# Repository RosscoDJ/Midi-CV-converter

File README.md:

# Midi-CV-converter
Arduino based Midi to CV converter, including selectable Midi channel.

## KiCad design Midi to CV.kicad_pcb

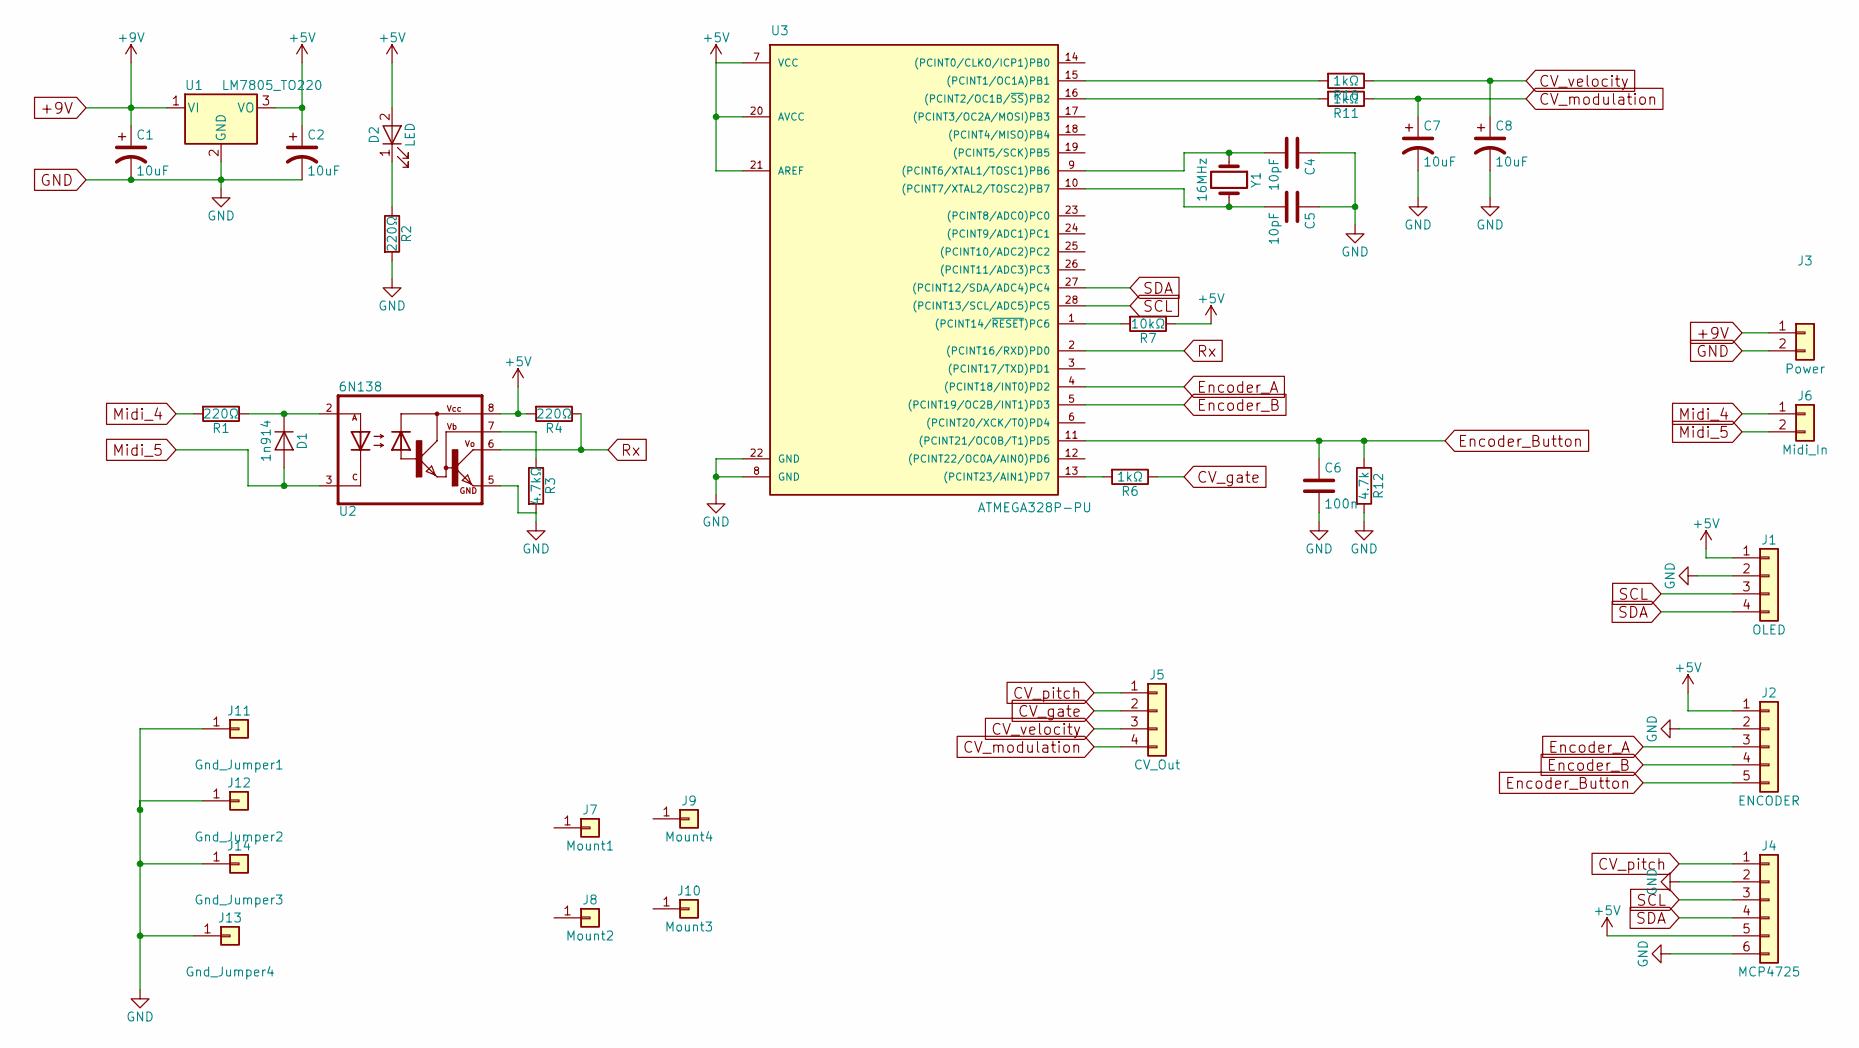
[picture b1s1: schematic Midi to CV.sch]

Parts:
C1, C2, C7, C8: 10uF; CP_Radial_D4.0mm_P1.50mm
C4, C5: 10pF; C_Disc_D6.0mm_W2.5mm_P5.00mm
C6: 100n; C_Disc_D6.0mm_W2.5mm_P5.00mm
D1: 1n914; D_DO-35_SOD27_P7.62mm_Horizontal
D2: LED; LED_D5.0mm
J1: OLED; Pin_Header_Straight_1x04_Pitch2.54mm
J2: ENCODER; Pin_Header_Straight_1x05_Pitch2.54mm
J3: Power; Pin_Header_Straight_1x02_Pitch2.54mm
J4: MCP4725; Pin_Header_Straight_1x06_Pitch2.54mm
J5: CV_Out; Pin_Header_Straight_1x04_Pitch2.54mm
J6: Midi_In; Pin_Header_Straight_1x02_Pitch2.54mm
J7: Mount1; MountingHole_3.2mm_M3
J8: Mount2; MountingHole_3.2mm_M3
J9: Mount4; MountingHole_3.2mm_M3
J10: Mount3; MountingHole_3.2mm_M3
J11: Gnd_Jumper1; Pin_Header_Straight_1x01_Pitch2.54mm
J12: Gnd_Jumper2; Pin_Header_Straight_1x01_Pitch2.54mm
J13: Gnd_Jumper4; Pin_Header_Straight_1x01_Pitch2.54mm
J14: Gnd_Jumper3; Pin_Header_Straight_1x01_Pitch2.54mm
R1, R2, R4: 220Ω; R_Axial_DIN0204_L3.6mm_D1.6mm_P7.62mm_Horizontal
R3: 4.7kΩ; R_Axial_DIN0204_L3.6mm_D1.6mm_P7.62mm_Horizontal
R6, R10, R11: 1kΩ; R_Axial_DIN0204_L3.6mm_D1.6mm_P7.62mm_Horizontal
R7: 10kΩ; R_Axial_DIN0204_L3.6mm_D1.6mm_P7.62mm_Horizontal
R12: 4.7k; R_Axial_DIN0204_L3.6mm_D1.6mm_P7.62mm_Horizontal
U1: LM7805_TO220; TO-220-3_Vertical
U2: 6N138; DIP-8_W7.62mm_LongPads
U3: ATMEGA328P-PU; DIP-28_W7.62mm_LongPads
Y1: 16MHz; Crystal_HC49-U_Vertical

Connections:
+5V: C2.1, D2.2 (A), J1.1, J2.1, J4.5, R4.2, R7.1, U1.3 (VO), U2.8 (VCC), U3.7 (VCC), U3.20 (AVCC), U3.21 (AREF)
+9V: C1.1, J3.1, U1.1 (VI)
CV_gate: J5.2, R6.1
CV_modulation: C7.1, J5.4, R11.1
CV_pitch: J4.1, J5.1
CV_velocity: C8.1, J5.3, R10.1
Encoder_A: J2.3, U3.4 ((PCINT18/INT0)PD2)
Encoder_B: J2.4, U3.5 ((PCINT19/OC2B/INT1)PD3)
Encoder_Button: C6.1, J2.5, R12.1, U3.11 ((PCINT21/OC0B/T1)PD5)
GND: C1.2, C2.2, C4.1, C5.1, C6.2, C7.2, C8.2, J1.2, J2.2, J3.2, J4.2, J4.6, J11.1, J12.1, J13.1, J14.1, R2.2, R3.2, R12.2, U1.2 (GND), U2.5 (GND), U3.8 (GND), U3.22 (GND)
Midi_4: J6.1, R1.2
Midi_5: D1.2 (A), J6.2, U2.3 (C)
unnamed: C4.2, U3.9 ((PCINT6/XTAL1/TOSC1)PB6), Y1.1
unnamed: C5.2, U3.10 ((PCINT7/XTAL2/TOSC2)PB7), Y1.2
unnamed: D1.1 (K), R1.1, U2.2 (A)
unnamed: D2.1 (K), R2.1
unnamed: R3.1, U2.7 (VB)
unnamed: R6.2, U3.13 ((PCINT23/AIN1)PD7)
unnamed: R7.2, U3.1 ((PCINT14/~RESET~)PC6)
unnamed: R10.2, U3.15 ((PCINT1/OC1A)PB1)
unnamed: R11.2, U3.16 ((PCINT2/OC1B/~SS~)PB2)
Rx: R4.1, U2.6 (VO), U3.2 ((PCINT16/RXD)PD0)
SCL: J1.3, J4.3, U3.28 ((PCINT13/SCL/ADC5)PC5)
SDA: J1.4, J4.4, U3.27 ((PCINT12/SDA/ADC4)PC4)

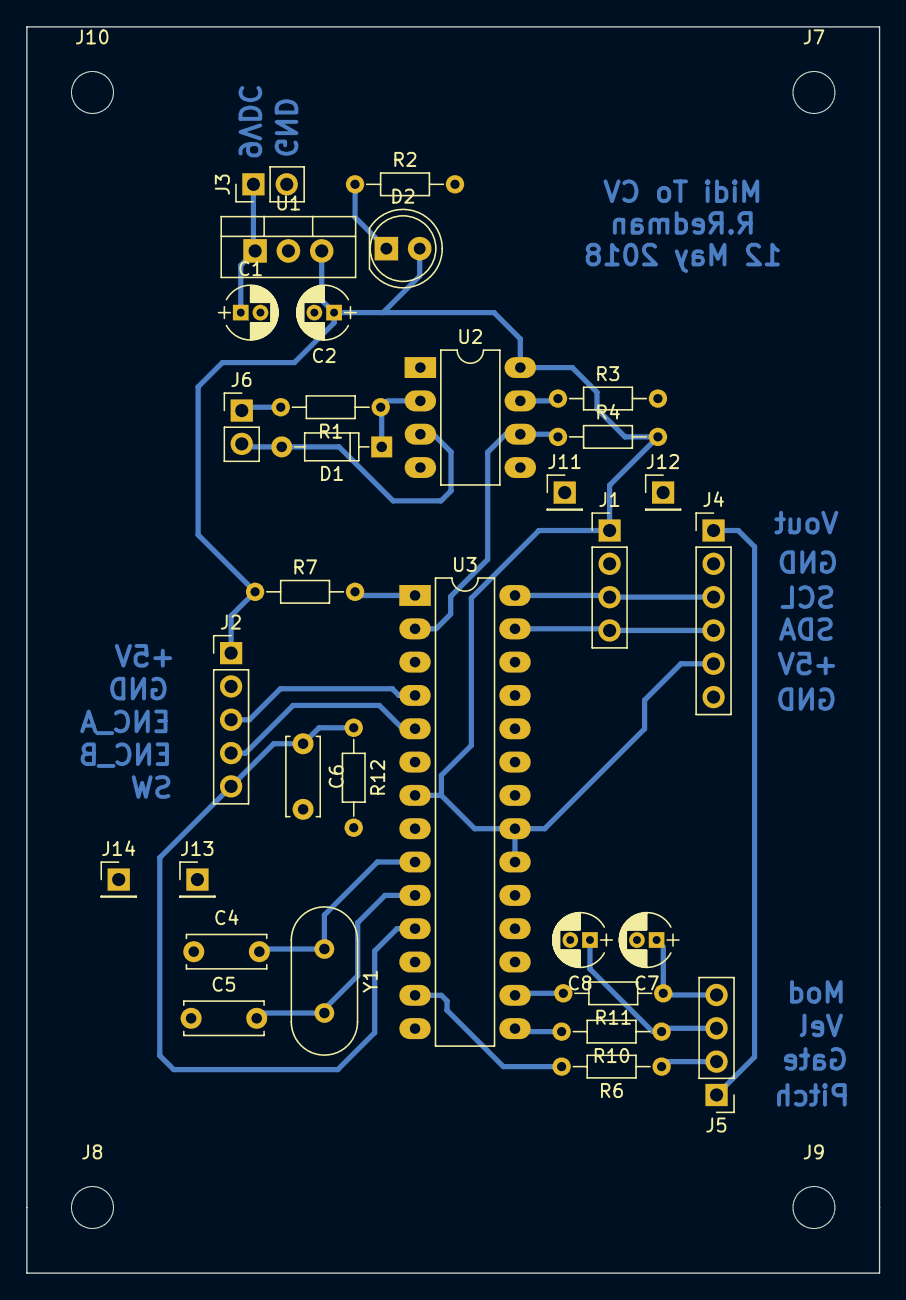
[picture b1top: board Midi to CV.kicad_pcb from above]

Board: 2 copper layers, 65.0 x 95.0 mm, 36 parts (0 on the bottom side), 24 nets.

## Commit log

2018-04-11 Add files via upload
    Midi2CV code
2018-04-11 Add files via upload
    Pinout listing for Arduino uno
2018-04-14 Add files via upload
    Added i2c Oled display of midi channel, and midi channel select asks to save via encoder push
2018-04-14 Delete AnotherMIDI2CVBox.ino
    Remove old LED file to replace with current Oled file
2018-04-14 Add files via upload
    Remove shift register and LED pin assignments
2018-04-14 Add files via upload
    Fix issue where Midi channel display couldn't keep up with fast scrolls of encoder.
2018-05-14 Add files via upload
    Update version of Arduino source code.
2018-05-14 Add files via upload
    Update pin assignments.
2018-05-14 Add files via upload
    add kicad files.
